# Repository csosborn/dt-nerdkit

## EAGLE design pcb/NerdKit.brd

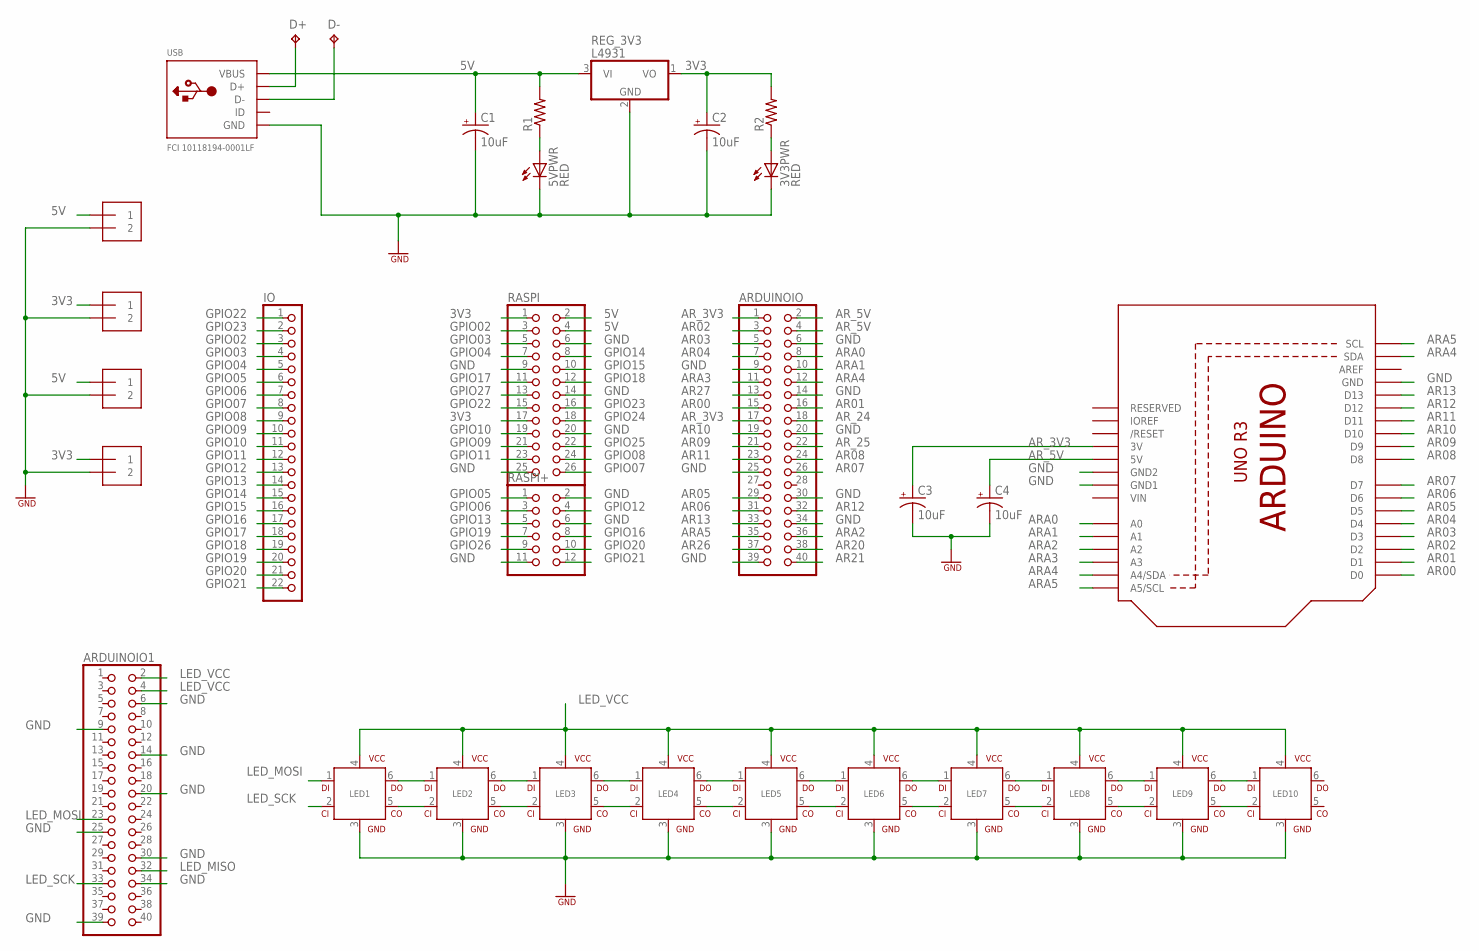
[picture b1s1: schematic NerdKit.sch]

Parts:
3V3PWR, 5VPWR: RED; LED3MM
ARDUINOIO, ARDUINOIO1: PINHD-2X20; 2X20
C1, C2, C3, C4: 10uF; E1,8-4
D+: TPPAD1-13; P1-13
D-: TPPAD1-13; P1-13
IO: PINHD-1X22; 1X22
LED1, LED2, LED3, LED4, LED5, LED6, LED7, LED8, LED9, LED10: RGBLED5050
PB1_TB_3V3, PB1_TB_5V, PB2_TB_3V3, PB2_TB_5V: 1X2-3.5MM
R1, R2: R-US_0207/7; 0207/7
RASPI: PINHD-2X13; 2X13
RASPI+: PINHD-2X6; 2X06
REG_3V3: L4931; TO92
U2: ARDUINOR3-PINSONLY; ARDUINOR3_PINSONLY
USB: FCI 10118194-0001LF; 4UCONN_20329

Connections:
3V3: C2.+, PB1_TB_3V3.1, PB2_TB_3V3.1, R2.2, RASPI.1, RASPI.17, REG_3V3.1 (VO)
5V: C1.+, PB1_TB_5V.1, PB2_TB_5V.1, R1.2, RASPI.2, RASPI.4, REG_3V3.3 (VI), USB.VBUS
AR00: ARDUINOIO.15, U2.D0
AR01: ARDUINOIO.16, U2.D1
AR02: ARDUINOIO.3, U2.D2
AR03: ARDUINOIO.5, U2.D3
AR04: ARDUINOIO.7, U2.D4
AR05: ARDUINOIO.29, U2.D5
AR06: ARDUINOIO.31, U2.D6
AR07: ARDUINOIO.26, U2.D7
AR08: ARDUINOIO.24, U2.D8
AR09: ARDUINOIO.21, U2.D9
AR10: ARDUINOIO.19, U2.D10
AR11: ARDUINOIO.23, U2.D11
AR12: ARDUINOIO.32, U2.D12
AR13: ARDUINOIO.33, U2.D13
AR20: ARDUINOIO.38
AR21: ARDUINOIO.40
AR26: ARDUINOIO.37
AR27: ARDUINOIO.13
ARA0: ARDUINOIO.8, U2.A0
ARA1: ARDUINOIO.10, U2.A1
ARA2: ARDUINOIO.36, U2.A2
ARA3: ARDUINOIO.11, U2.A3
ARA4: ARDUINOIO.12, U2.A4 (A4/SDA), U2.SDA
ARA5: ARDUINOIO.35, U2.A5 (A5/SCL), U2.SCL
AR_3V3: ARDUINOIO.1, ARDUINOIO.17, C3.+, U2.3V
AR_5V: ARDUINOIO.2, ARDUINOIO.4, C4.+, U2.5V
AR_24: ARDUINOIO.18
AR_25: ARDUINOIO.22
GND: 3V3PWR.K (C), 5VPWR.K (C), ARDUINOIO.6, ARDUINOIO.9, ARDUINOIO.14, ARDUINOIO.20, ARDUINOIO.25, ARDUINOIO.30, ARDUINOIO.34, ARDUINOIO.39, ARDUINOIO1.6, ARDUINOIO1.9, ARDUINOIO1.14, ARDUINOIO1.20, ARDUINOIO1.25, ARDUINOIO1.30, ARDUINOIO1.34, ARDUINOIO1.39, C1.-, C2.-, C3.-, C4.-, LED1.3 (GND), LED2.3 (GND), LED3.3 (GND), LED4.3 (GND), LED5.3 (GND), LED6.3 (GND), LED7.3 (GND), LED8.3 (GND), LED9.3 (GND), LED10.3 (GND), PB1_TB_3V3.2, PB1_TB_5V.2, PB2_TB_3V3.2, PB2_TB_5V.2, RASPI.6, RASPI.9, RASPI.14, RASPI.20, RASPI.25, RASPI+.2, RASPI+.6, RASPI+.11, REG_3V3.2 (GND), U2.GND, U2.GND1, U2.GND2, USB.BASE@1 (GND), USB.BASE@2 (GND), USB.GND, USB.SPRT@1 (GND), USB.SPRT@2 (GND), USB.SPRT@3 (GND), USB.SPRT@4 (GND)
GPIO02: IO.3, RASPI.3
GPIO03: IO.4, RASPI.5
GPIO04: IO.5, RASPI.7
GPIO05: IO.6, RASPI+.1
GPIO06: IO.7, RASPI+.3
GPIO07: IO.8, RASPI.26
GPIO08: IO.9, RASPI.24
GPIO09: IO.10, RASPI.21
GPIO10: IO.11, RASPI.19
GPIO11: IO.12, RASPI.23
GPIO12: IO.13, RASPI+.4
GPIO13: IO.14, RASPI+.5
GPIO14: IO.15, RASPI.8
GPIO15: IO.16, RASPI.10
GPIO16: IO.17, RASPI+.8
GPIO17: IO.18, RASPI.11
GPIO18: IO.19, RASPI.12
GPIO19: IO.20, RASPI+.7
GPIO20: IO.21, RASPI+.10
GPIO21: IO.22, RASPI+.12
GPIO22: IO.1, RASPI.15
GPIO23: IO.2, RASPI.16
GPIO24: RASPI.18
GPIO25: RASPI.22
GPIO26: RASPI+.9
GPIO27: RASPI.13
LED_MISO: ARDUINOIO1.32
LED_MOSI: ARDUINOIO1.23, LED1.1 (DI)
LED_SCK: ARDUINOIO1.33, LED1.2 (CI)
LED_VCC: ARDUINOIO1.2, ARDUINOIO1.4, LED1.4 (VCC), LED2.4 (VCC), LED3.4 (VCC), LED4.4 (VCC), LED5.4 (VCC), LED6.4 (VCC), LED7.4 (VCC), LED8.4 (VCC), LED9.4 (VCC), LED10.4 (VCC)
unnamed: 3V3PWR.A, R2.1
unnamed: D+.TP, USB.D+
unnamed: LED1.6 (DO), LED2.1 (DI)
unnamed: LED1.5 (CO), LED2.2 (CI)
unnamed: LED2.6 (DO), LED3.1 (DI)
unnamed: LED2.5 (CO), LED3.2 (CI)
unnamed: LED3.6 (DO), LED4.1 (DI)
unnamed: LED3.5 (CO), LED4.2 (CI)
unnamed: LED4.6 (DO), LED5.1 (DI)
unnamed: LED4.5 (CO), LED5.2 (CI)
unnamed: LED5.6 (DO), LED6.1 (DI)
unnamed: LED5.5 (CO), LED6.2 (CI)
unnamed: LED6.6 (DO), LED7.1 (DI)
unnamed: LED6.5 (CO), LED7.2 (CI)
unnamed: LED7.6 (DO), LED8.1 (DI)
unnamed: LED7.5 (CO), LED8.2 (CI)
unnamed: LED8.6 (DO), LED9.1 (DI)
unnamed: LED8.5 (CO), LED9.2 (CI)
unnamed: LED9.6 (DO), LED10.1 (DI)
unnamed: LED9.5 (CO), LED10.2 (CI)
unnamed: D-.TP, USB.D-
unnamed: 5VPWR.A, R1.1
VIN: U2.VIN

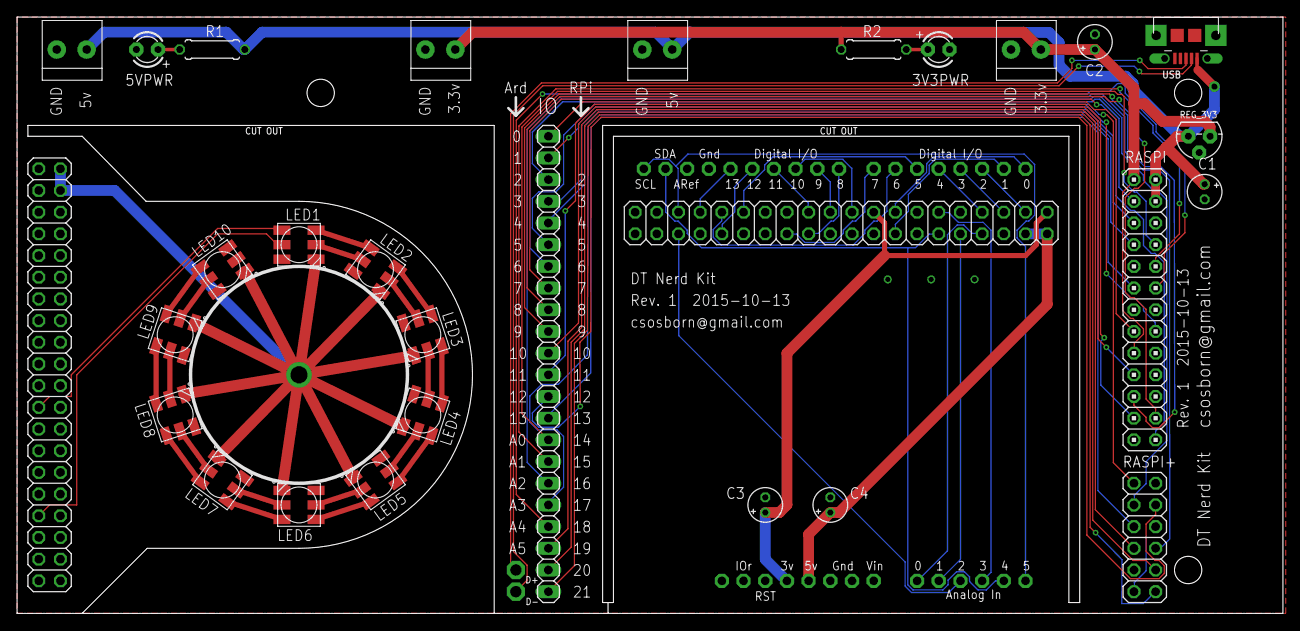
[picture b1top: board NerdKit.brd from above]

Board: 2 copper layers, 148.2 x 69.8 mm, 32 parts (0 on the bottom side), 72 nets.

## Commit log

2015-11-05 Initial commit, including Rev 1 of the PCB.
2015-11-29 Added .gitignore file.
    Ignoring the files produced by EAGLE autorouter runs.
2015-11-29 Corrected the header orientation on the Arduino shield adapter card.
2015-11-29 Corrected the header orientation on the secondary LED card.
2015-11-29 Adjusted power terminal blocks and associated components 0.1" inboard.
    Fixes #2.
2015-11-29 Corrected schematic error on LED6 ground pin and adjusted copper pour.
    Fixes #7.
2015-11-29 Added OSH Park compliant cutouts for daughter cards.
    See http://docs.oshpark.com/submitting-orders/cutouts-and-slots/.
2015-12-04 Ditched the 2.1mm DC jack and regulator in favor of micro USB for power.
    This fixes #5.
2015-12-04 Added mounting holes.
    Also brought the USB D+ and D- signals out to test points, just for fun.
2015-12-05 Lots of trace cleanup and local optimizations.
